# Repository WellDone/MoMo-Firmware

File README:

This file should eventually contain things.

TODO
1.  Fix the alarm handler in the rtcc code to have a common interrupt handler
    and store a pointer to the command to execute.
2.  Add rtcc commands to serial terminal
3.  Add SPI talking to flash memory

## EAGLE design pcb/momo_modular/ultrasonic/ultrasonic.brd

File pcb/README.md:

# MoMo Printed Circuit Boards
This directory contains all of the MoMo PCB files as well as scripts used to convert them into production data.
All boards must use EAGLE CAD for layout in order to be compatible with our production scripts.

## PCB Layout
The MoMo build system includes a set of python based tools used to automatically generate production files, BOMS 
and cost estimates from EAGLE board files.  In order for a board to be compatible with these scripts, it
must be made to conform with the following requirements.

EAGLE Attributes are used to tag each part and board with metadata that enables the scripts to look up
information on the part using the Octopart API and to generate a BOM.  Each part should have one of following attributes:

 * _DIGIKEY-PN_ - This should contain the Digikey part number for this part.  If there is not a digikey part number, is should
be left blank or non existent
 * _MPN_ - This is the Manufacturer's part number for the part.  Either MPN or DIGIKEY-PN must be set for every part on the board that
should be populated.
 * _MANU_ - The manufacturer's name.  If MPN is used to specify the part, MANU should be specified as well.
 * _FOOTPRINT_ - If the part does not have a standard SMD footprint link 0402, 0603, etc, they FOOTPRINT should be explicitly defined so
 that it can be used to create a BOM automatically.  If this is a through hole part, the footprint should be given as "Through Hole"
 * _DESC_ - If the part cannot have a generic description made for it (currently only works for Resistors, Capacitors and Inductors)
 then the explicit description should be given in this attribute.

###Assembly Variants
In order to save on PCB fabrication costs, sometimes a single circuit board will be made flexible so that it can be customized at assembly
time by simply change or not populating certain parts.  Each different way the same board can be assembled is called an Assembly Variant.

If a board has several assembly variants, this should be indicated by specifying certain attributes on the board.  An assembly variant can 
either populate a certain part, not populate a certain part or replace a part with a different one.  To do this, change the DIGIKEY-PN or MPN attribute for the part to contain -VARIANT where variant is the name of the assembly variant.  A part with only DIGIKEY-PN (or MPN) set will be assumed to be populated
in every assembly variant. A part with DIGIKEY-PN-VAR1 and DIGIKEY-PN-VAR2 will be populated only in Assembly Variants VAR1 and VAR2.  

A part with DIGIKEY-PN will be populated in every assembly variant except those that have a DIGIKEY-PN-VAR1 with an empty value.  This
means that the way to not populate a certain part in an assembly variant is to define its part number to be blank.  For library parts
that contain a default DIGIKEY-PN value that is not deletable, this is the only way to not populate a part in an assembly variant.

####Changing Part Values in Different Assembly Variants
Often a different assembly variant will not just populate or depopulate a part, but will change a part's value in order to achieve the desired effect.  
For example, a buck regulator design that can be configured to output either 3.6 or 5V depending on the assembly variant may require just changing the feedback resistor value.
In order to do this, the value should be specified as a VALUE attribute with the appropriate -VARIANT name.  So, if there are 2 assembly variants, 5V and 3V and a resistor is 10K in the 
5V version and 15K in the 3V version, the resistor should have the following two attributes:
VALUE-5V = 10K
VALUE-3V = 15K
The actual value of the part may be set to anything since it will be overriden by these attributes.  It is recommended that the actual part value be set to 'varies' so that the 
schematic's intent is not confusing.
###Global Attributes
Every board must define the following global attributes.  These should be defined on the Board, not the Schematic, under Edit->Global Attributes:

 * _[VARIANT]_ - for each assembly variant (if there is only one, nothing must be done) with value ASSY-VARIANT.  The attribute name is the variant name
 * _WIDTH_ - the width of the board (in inches)
 * _HEIGHT_ - the height of the board (in inches)
 * _REVISION_ - a tag specifying the revision level of the board
 * _PARTNAME_ - a name for the board that will be used to generate file names

###Required Configuration
In order to use these scripts you need to configure the location of the Eagle binary on your computer in /config/settings.local.json.  Use the template provided in:
settings.global.json

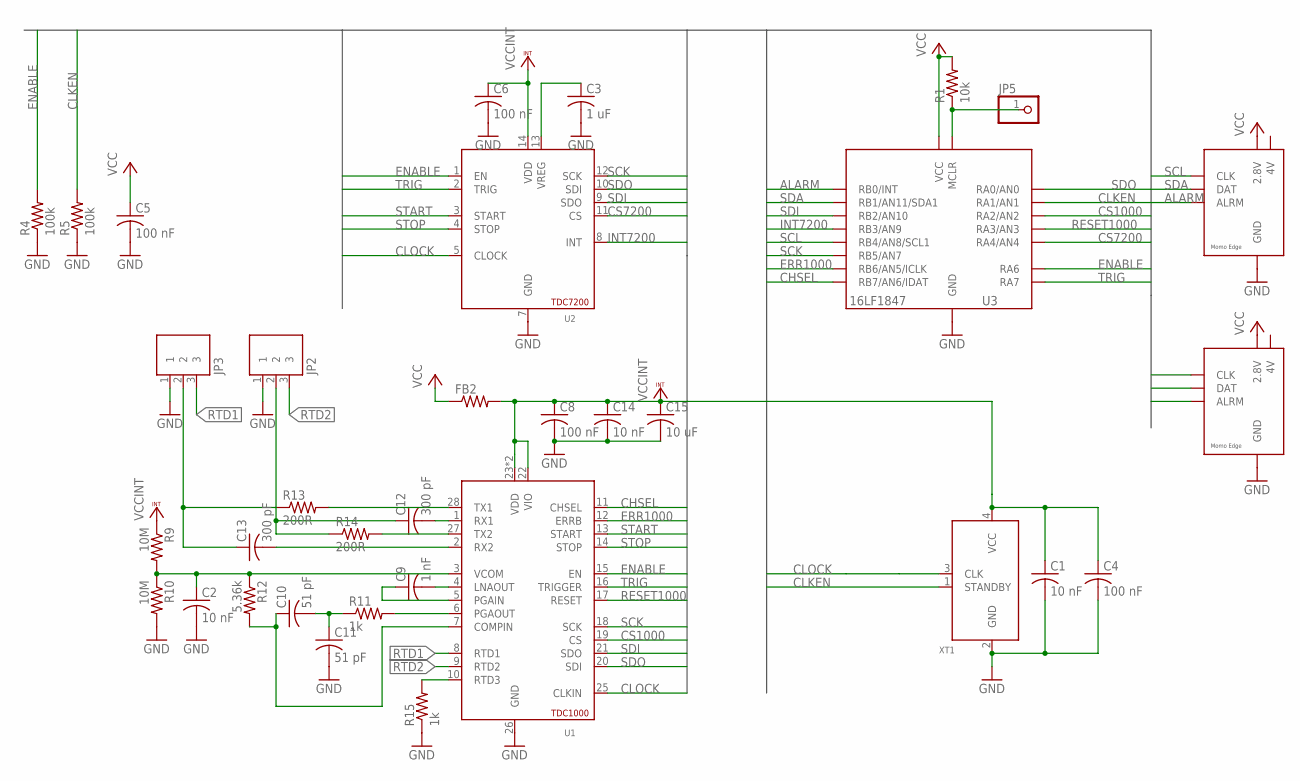
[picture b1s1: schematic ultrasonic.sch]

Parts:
C1, C2, C14: 10 nF; C0402; DIGIKEY-PN 490-4516-1-ND
C3: 1 uF; C0402; DIGIKEY-PN 490-3890-1-ND
C4, C5, C6, C8: 100 nF; C0402; DIGIKEY-PN 490-1318-1-ND
C9: 1 nF; C0402; DIGIKEY-PN 490-6349-1-ND
C10, C11: 51 pF; C0402; DIGIKEY-PN 490-5944-1-ND
C12, C13: 300 pF; C0402; DIGIKEY-PN 490-3234-1-ND
C15: 10 uF; C0805K; DIGIKEY-PN 490-10516-1-ND
FB2: R-US_R0603; R0603
JP1: MOMO-VERT-6M; 1X06
JP2, JP3: JST-PH-3PIN
JP4: MOMO-EDGE-6M-RIGHT; MOMO-EDGE-6M
JP5: PINHD-1X1; 1X01
R1: 10k; R0402; DIGIKEY-PN RHM10.0KCDCT-ND
R4, R5: 100k; R0402; DIGIKEY-PN RHM100KCDCT-ND
R9, R10: 10M; R0402; DIGIKEY-PN 1276-3434-1-ND
R11: 1k; R0402; DIGIKEY-PN RHM1.00KCDCT-ND
R12: 5.36k; R0402; DIGIKEY-PN RHM5.36KCDCT-ND
R13, R14: 200R; R0402; DIGIKEY-PN 311-200LRCT-ND
R15: 1k; R0402; DIGIKEY-PN P1.0KDCCT-ND
U1: TDC1000; TSSOP28; MPN TDC1000PW
U2: TDC7200; TSSOP14; MPN TDC7200PW
U3: PIC16LF1847; SSOP20
XT1: MEMS-OSCILLATOR; 4-DFN

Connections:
4V: JP1.6 (4V), JP4.CLK (4V)
ALARM: JP1.5 (ALRM), JP4.DAT (ALRM), U3.7 (RB0/INT)
CHSEL: U1.11 (CHSEL), U3.14 (RB7/AN6/IDAT)
CLKEN: R5.2, U3.20 (RA1/AN1), XT1.1 (STANDBY)
CLOCK: U1.25 (CLKIN), U2.5 (CLOCK), XT1.3 (CLK)
CS1000: U1.19 (CS), U3.1 (RA2/AN2)
CS7200: U2.11 (CS), U3.3 (RA4/AN4)
ENABLE: R4.2, U1.15 (EN), U2.1 (EN), U3.17 (RA6)
ERR1000: U1.12 (ERRB), U3.13 (RB6/AN5/ICLK)
GND: C1.2, C2.2, C3.2, C4.2, C5.2, C6.2, C8.2, C11.2, C14.2, C15.2, JP1.7 (GND), JP2.1, JP3.1, JP4.V28 (GND), R4.1, R5.1, R10.2, R15.1, U1.26 (GND), U2.7 (GND), U3.5 (GND), U3.6 (GND), XT1.2 (GND)
INT7200: U2.8 (INT), U3.10 (RB3/AN9)
unnamed: C3.1, U2.13 (VREG)
unnamed: C9.2, U1.4 (LNAOUT)
unnamed: JP5.1, R1.1, U3.4 (MCLR)
unnamed: C2.1, R9.2, R10.1, R12.1, U1.3 (VCOM)
unnamed: C9.1, U1.5 (PGAIN)
unnamed: C10.2, C11.1, R11.1
unnamed: R11.2, U1.6 (PGAOUT)
unnamed: C10.1, R12.2, U1.7 (COMPIN)
unnamed: C13.1, JP3.2, R13.1
unnamed: R14.2, U1.27 (TX2)
unnamed: R13.2, U1.28 (TX1)
unnamed: C12.2, U1.1 (RX1)
unnamed: C13.2, U1.2 (RX2)
unnamed: C12.1, JP2.2, R14.1
unnamed: R15.2, U1.10 (RTD3)
RESET1000: U1.17 (RESET), U3.2 (RA3/AN3)
RTD1: JP3.3, U1.8 (RTD1)
RTD2: JP2.3, U1.9 (RTD2)
SCK: U1.18 (SCK), U2.12 (SCK), U3.12 (RB5/AN7)
SCL: JP1.3 (CLK), JP4.4V (CLK), U3.11 (RB4/AN8/SCL1)
SDA: JP1.4 (DAT), JP4.ALARM (DAT), U3.8 (RB1/AN11/SDA1)
SDI: U1.21 (SDO), U2.9 (SDO), U3.9 (RB2/AN10)
SDO: U1.20 (SDI), U2.10 (SDI), U3.19 (RA0/AN0)
START: U1.13 (START), U2.3 (START)
STOP: U1.14 (STOP), U2.4 (STOP)
TRIG: U1.16 (TRIGGER), U2.2 (TRIG), U3.18 (RA7)
VCC: C5.1, FB2.1, JP1.1 (2.8V), JP4.GND (2.8V), R1.2, U3.15 (VCC), U3.16 (VCC)
VCCINT: C1.1, C4.1, C6.1, C8.1, C14.1, C15.1, FB2.2, R9.1, U1.22 (VIO), U1.23 (VDD), U1.24 (VDD), U2.14 (VDD), XT1.4 (VCC)

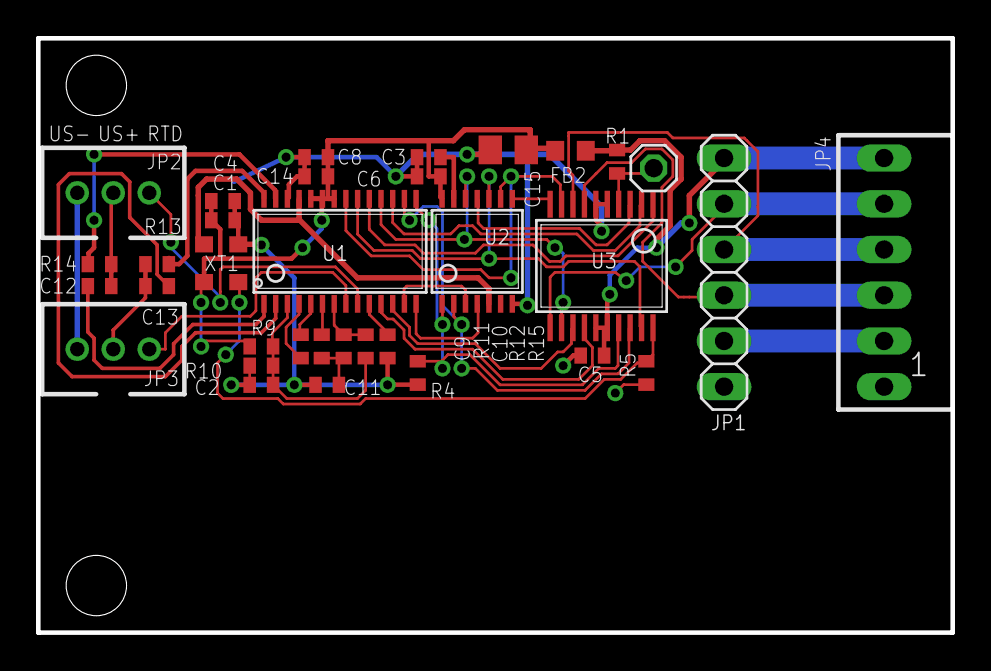
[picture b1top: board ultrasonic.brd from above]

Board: 2 copper layers, 50.8 x 33.0 mm, 34 parts (0 on the bottom side), 39 nets.

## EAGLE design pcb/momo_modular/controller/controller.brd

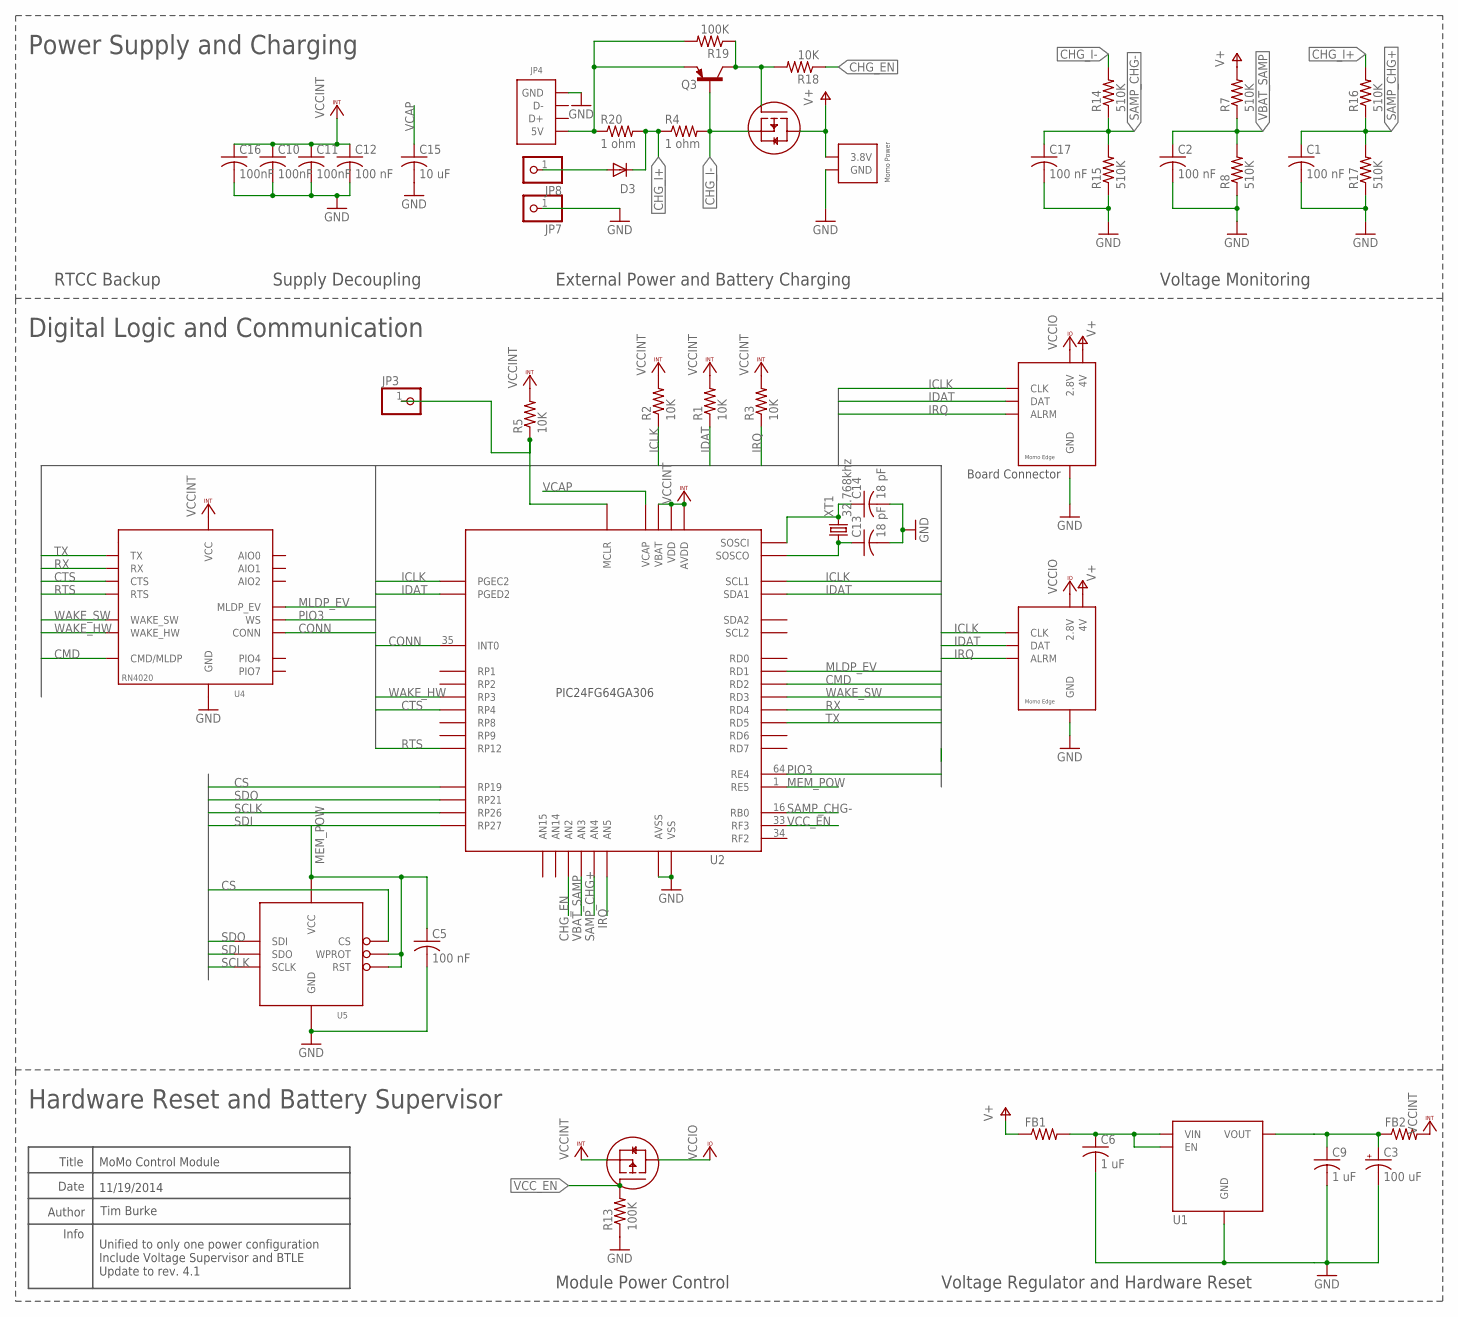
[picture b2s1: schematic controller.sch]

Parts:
C1, C2, C5, C12, C17: 100 nF; C0402K; DIGIKEY-PN 445-1265-1-ND
C3: 100 uF; B/3528-21R; DIGIKEY-PN 478-8156-1-ND
C6, C9: 1 uF; C0402K; DIGIKEY-PN 445-4114-1-ND
C10, C11, C16: 100nF; C0402K; DIGIKEY-PN 445-1265-1-ND
C13, C14: 18 pF; C0402K; DIGIKEY-PN 445-1238-1-ND
C15: 10 uF; C0805K; DIGIKEY-PN 1276-2893-1-ND
D3: DIODE-SC79_INFINEON; SC79_INFINEON
FB1, FB2: R-US_R0603; R0603; DIGIKEY-PN 490-5981-1-ND
JP1: MOMO-VERT-6M; 1X06; DIGIKEY-PN S1011EC-06-ND
JP2: MOMO-EDGE-6F; MOMO-EDGE-8F
JP3, JP7, JP8: PINHD-1X1; 1X01
JP4: CONN-MICROUSB-B-RCPT; MICROUSB-B-FCI
JP5: MOMO-PWR-HOUSED
Q2, Q4: P-MOSFET; SOT23; DIGIKEY-PN IRLML6402PBFCT-ND
Q3: MMBTA56-SOT23; SOT23; DIGIKEY-PN 568-1742-1-ND
R1, R2, R3, R5, R18: 10K; R0603; DIGIKEY-PN P10.0KHCT-ND
R4, R20: 1 ohm; R1206; DIGIKEY-PN 311-1.00FRCT-ND
R7, R8, R14, R15, R16, R17: 510K; R0603; DIGIKEY-PN P510KHCT-ND
R13, R19: 100K; R0603; DIGIKEY-PN P100KHCT-ND
U1: XC6504-LINEAR-REGULATOR; SOT23-5L
U2: PIC24FJ64GA306; TQFP64-10X10
U4: RN4020_BT_4.0_MODULE; RN20-BTLE-MODULE; DIGIKEY-PN RN4020-V/RM120-ND
U5: FLASH8MSOP8; SOP08; DIGIKEY-PN M25PX80-VMN6TPCT-ND
XT1: 32.768khz; TC26H; DIGIKEY-PN 535-9034-ND

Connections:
CHG_EN: R18.1, U2.14 (AN2)
CHG_I+: D3.C, R4.1, R16.2, R20.2
CHG_I-: Q3.1 (B), Q4.2 (SOURCE), R4.2, R14.2
CMD: U2.50 (RD2), U4.CMD/MLDP
CONN: U2.35 (INT0), U4.PIO1 (CONN)
CS: U2.6 (RP19), U5.1 (CS)
CTS: U2.43 (RP4), U4.PIO5 (CTS)
GND: C1.2, C2.2, C3.-, C5.2, C6.2, C9.2, C10.2, C11.2, C12.2, C13.2, C14.2, C15.2, C16.2, C17.2, JP1.7 (GND), JP2.GND, JP4.5 (GND), JP4.GND2 (GND), JP4.GND3 (GND), JP4.GND4 (GND), JP4.GND5 (GND), JP4.GND6 (GND), JP5.2 (GND), JP7.1, R8.1, R13.1, R15.1, R17.1, U1.2 (GND), U2.9 (VSS), U2.20 (AVSS), U2.25 (VSS), U2.41 (VSS), U4.GND, U4.GND1 (GND), U4.SHIELD1 (GND), U4.SHIELD2 (GND), U4.SHIELD3 (GND), U4.SHIELD4 (GND), U5.4 (GND)
ICLK: JP1.3 (CLK), JP2.CLK, R2.1, U2.17 (PGEC2), U2.37 (SCL1)
IDAT: JP1.4 (DAT), JP2.DAT, R1.1, U2.18 (PGED2), U2.36 (SDA1)
IRQ: JP1.5 (ALRM), JP2.ARLM (ALRM), R3.1, U2.11 (AN5)
MEM_POW: C5.1, U2.1 (RE5), U5.3 (WPROT), U5.7 (RST), U5.8 (VCC)
MLDP_EV: U2.49 (RD1), U4.PIO2 (MLDP_EV)
unnamed: C3.+, C9.1, FB2.1, U1.5 (VOUT)
unnamed: C6.1, FB1.2, U1.1 (VIN), U1.3 (EN)
unnamed: D3.A, JP8.1
unnamed: JP3.1, R5.1, U2.7 (MCLR)
unnamed: JP4.1 (5V), Q3.2 (E), R19.2, R20.1
unnamed: C14.1, U2.47 (SOSCI), XT1.2
unnamed: C13.1, U2.48 (SOSCO), XT1.1
unnamed: Q3.3 (C), Q4.1 (GATE), R18.2, R19.1
PIO3: U2.64 (RE4), U4.PIO3 (WS)
RTS: U2.45 (RP12), U4.RTS/PIO6 (RTS)
RX: U2.52 (RD4), U4.UART_RX (RX)
SAMP_CHG+: C1.1, R16.1, R17.2, U2.12 (AN4)
SAMP_CHG-: C17.1, R14.1, R15.2, U2.16 (RB0)
SCLK: U2.5 (RP26), U5.6 (SCLK)
SDI: U2.8 (RP27), U5.2 (SDO)
SDO: U2.4 (RP21), U5.5 (SDI)
TX: U2.53 (RD5), U4.UART_TX (TX)
V+: FB1.1, JP1.6 (4V), JP2.V4 (4V), JP5.1 (3.8V), Q4.3 (DRAIN), R7.2
VBAT_SAMP: C2.1, R7.1, R8.2, U2.13 (AN3)
VCAP: C15.1, U2.56 (VCAP)
VCCINT: C10.1, C11.1, C12.1, C16.1, FB2.2, Q2.2 (SOURCE), R1.2, R2.2, R3.2, R5.2, U2.10 (VDD), U2.19 (AVDD), U2.26 (VDD), U2.38 (VDD), U2.57 (VBAT), U4.VDD (VCC)
VCCIO: JP1.1 (2.8V), JP2.V28 (2.8V), Q2.3 (DRAIN)
VCC_EN: Q2.1 (GATE), R13.2, U2.33 (RF3)
WAKE_HW: U2.44 (RP3), U4.WAKE_HW
WAKE_SW: U2.51 (RD3), U4.WAKE_SW

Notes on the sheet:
Title
Author
Date
Tim Burke
Info
Board Connector
MoMo Control Module
11/19/2014
Unified to only one power configuration Include Voltage Supervisor and BTLE Update to rev. 4.1
Power Supply and Charging
Digital Logic and Communication
Voltage Monitoring
External Power and Battery Charging
Supply Decoupling
RTCC Backup
Hardware Reset and Battery Supervisor
Module Power Control
Voltage Regulator and Hardware Reset

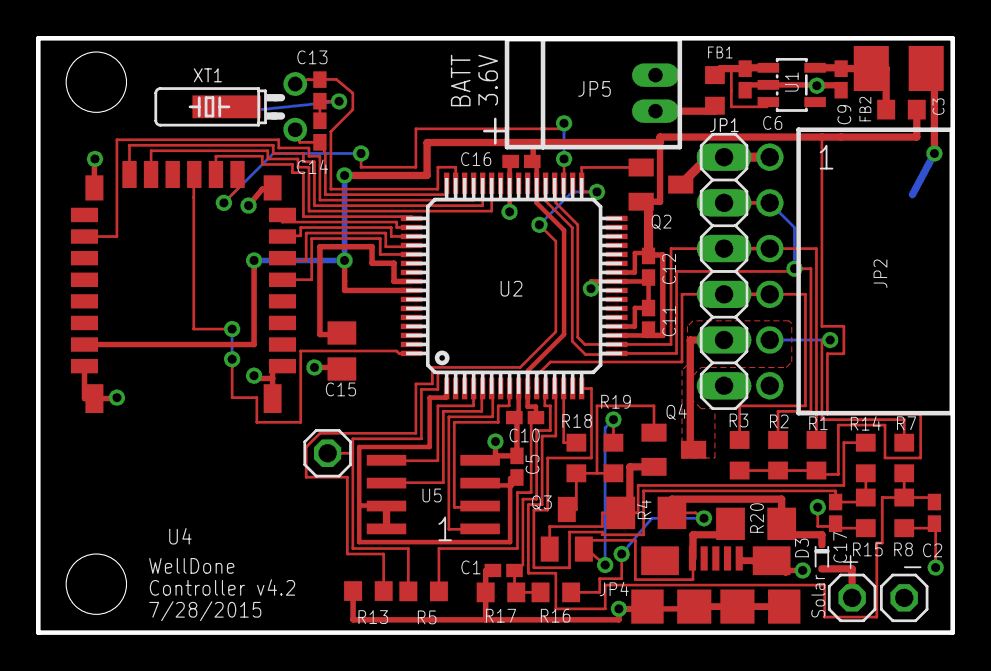
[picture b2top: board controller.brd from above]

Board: 2 copper layers, 50.8 x 33.0 mm, 47 parts (0 on the bottom side), 38 nets.

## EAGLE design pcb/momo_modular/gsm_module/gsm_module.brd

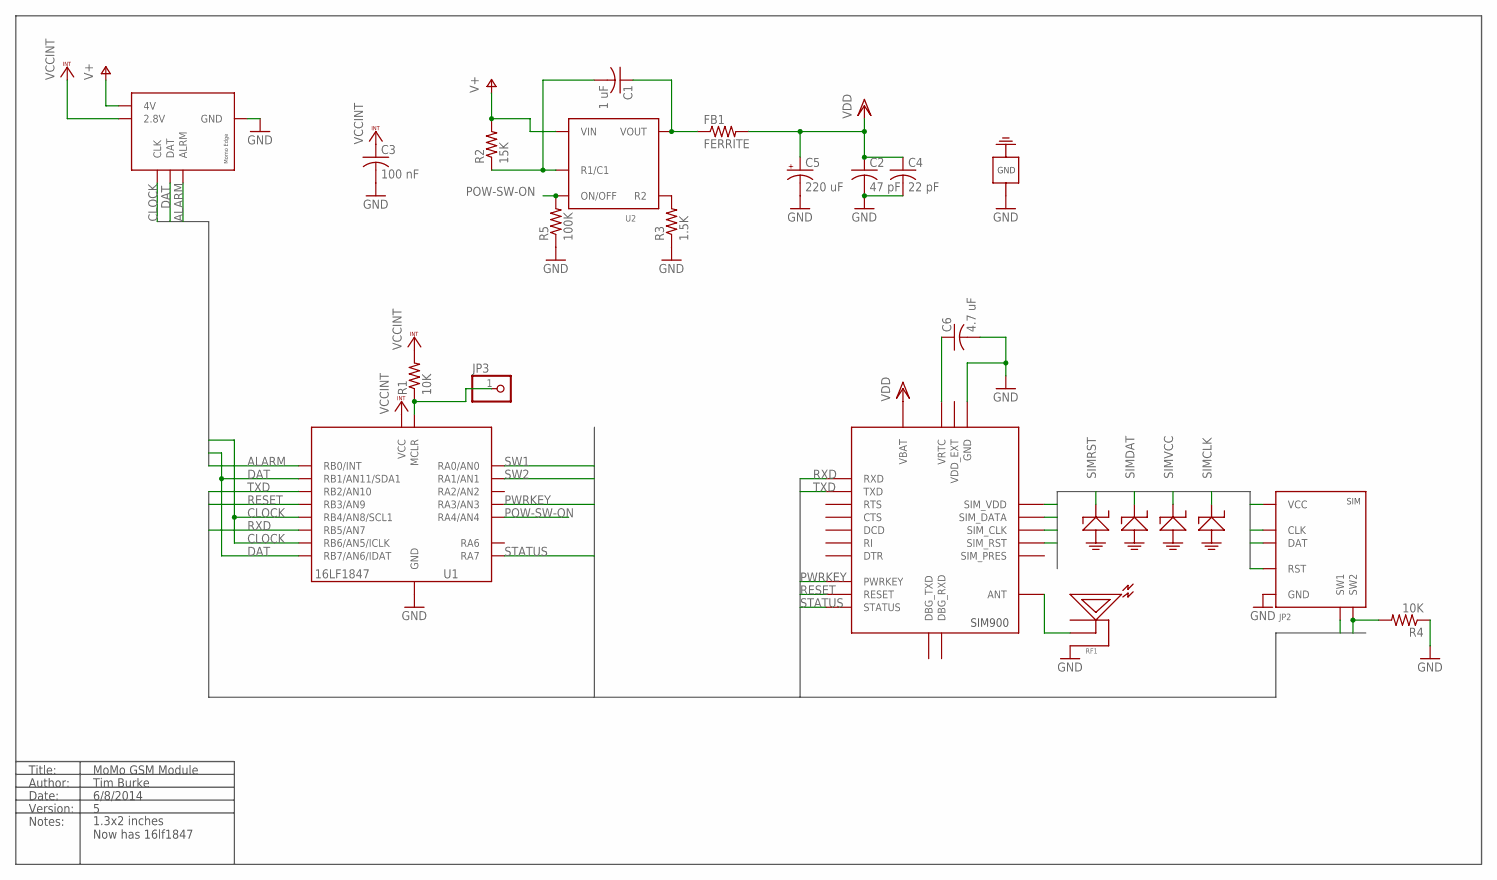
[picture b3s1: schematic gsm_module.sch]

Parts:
C1: 1 uF; C0402K; DIGIKEY-PN 445-4114-1-ND
C2: 47 pF; C0402K; DIGIKEY-PN 445-1243-1-ND
C3: 100 nF; C0402; DIGIKEY-PN 445-1265-1-ND
C4: 22 pF; C0402K; DIGIKEY-PN 445-1239-1-ND
C5: 220 uF; CT3528
C6: 4.7 uF; C0805; DIGIKEY-PN 1276-1259-1-ND
FB1: FERRITE; R0805; DIGIKEY-PN 445-1567-1-ND
JP1: MOMO-EDGE-6M
JP2: SIMHOLDER-8PINMICROSIM; MOLEX-MICROSIM-0787270001
JP3: PINHD-1X1; 1X01
R1, R4: 10K; R0603; DIGIKEY-PN P10.0KHCT-ND
R2: 15K; R0603; DIGIKEY-PN P15KGCT-ND
R3: 1.5K; R0603; DIGIKEY-PN P1.5KGCT-ND
R5: 100K; R0603; DIGIKEY-PN P100KHCT-ND
RF1: RFANTENNA; RFJACK; DIGIKEY-PN J983CT-ND
U1: PIC16LF1847; SSOP20
U2: TI-HIGHSIDE-PFET; SOT23-6L
U3: SIM900
U4: ESD-SMF05C; SC70-6L

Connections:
ALARM: JP1.ALARM (ALRM), U1.7 (RB0/INT)
CLOCK: JP1.CLK, U1.11 (RB4/AN8/SCL1), U1.13 (RB6/AN5/ICLK)
DAT: JP1.DAT, U1.8 (RB1/AN11/SDA1), U1.14 (RB7/AN6/IDAT)
GND: C2.2, C3.2, C4.2, C5.-, C6.2, JP1.GND, JP2.C5 (GND), JP2.GND1 (GND), JP2.GND2 (GND), JP2.GND3 (GND), JP2.GND4 (GND), JP2.GND5 (GND), JP2.GND6 (GND), R3.1, R4.1, R5.1, RF1.UNUSED1 (SHIELD), RF1.UNUSED2 (SHIELD), U1.5 (GND), U1.6 (GND), U3.17 (GND), U3.18 (GND), U3.29 (GND), U3.39 (GND), U3.45 (GND), U3.46 (GND), U3.53 (GND), U3.54 (GND), U3.58 (GND), U3.59 (GND), U3.61 (GND), U3.62 (GND), U3.63 (GND), U3.64 (GND), U3.65 (GND), U4.2 (GND)
unnamed: R3.2, U2.1 (R2)
unnamed: JP3.1, R1.1, U1.4 (MCLR)
unnamed: C1.2, R2.1, U2.6 (R1/C1)
unnamed: C1.1, FB1.1, U2.2 (VOUT), U2.3 (VOUT)
unnamed: C6.1, U3.26 (VRTC)
unnamed: RF1.ANTENNA (PIN), U3.60 (ANT)
POW-SW-ON: R5.2, U1.3 (RA4/AN4), U2.5 (ON/OFF)
PWRKEY: U1.2 (RA3/AN3), U3.1 (PWRKEY)
RESET: U1.10 (RB3/AN9), U3.16 (RESET)
RXD: U1.12 (RB5/AN7), U3.10 (RXD)
SIMCLK: JP2.C3 (CLK), U3.32 (SIM_CLK), U4.3
SIMDAT: JP2.C7 (DAT), U3.31 (SIM_DATA), U4.5
SIMRST: JP2.C2 (RST), U3.33 (SIM_RST), U4.1
SIMVCC: JP2.C1 (VCC), U3.30 (SIM_VDD), U4.4
STATUS: U1.18 (RA7), U3.66 (STATUS)
SW1: JP2.DCONT (SW1), U1.19 (RA0/AN0)
SW2: JP2.DSPRING (SW2), R4.2, U1.20 (RA1/AN1)
TXD: U1.9 (RB2/AN10), U3.9 (TXD)
V+: JP1.4V, R2.2, U2.4 (VIN)
VCCINT: C3.1, JP1.V28 (2.8V), R1.2, U1.15 (VCC), U1.16 (VCC)
VDD: C2.1, C4.1, C5.+, FB1.2, U3.55 (VBAT), U3.56 (VBAT), U3.57 (VBAT)
VDD_EXT: U3.15 (VDD_EXT)

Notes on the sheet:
Title:
Author:
Date:
Version:
Notes:
MoMo GSM Module
Tim Burke
6/8/2014
1.3x2 inches Now has 16lf1847

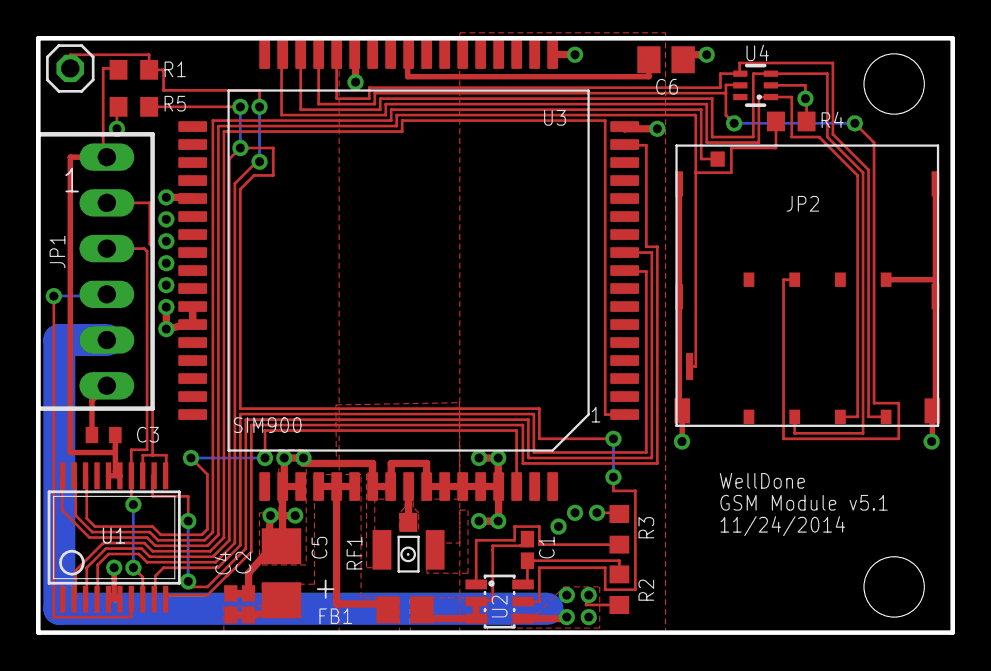
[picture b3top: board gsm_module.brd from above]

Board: 2 copper layers, 50.8 x 33.0 mm, 20 parts (0 on the bottom side), 25 nets.

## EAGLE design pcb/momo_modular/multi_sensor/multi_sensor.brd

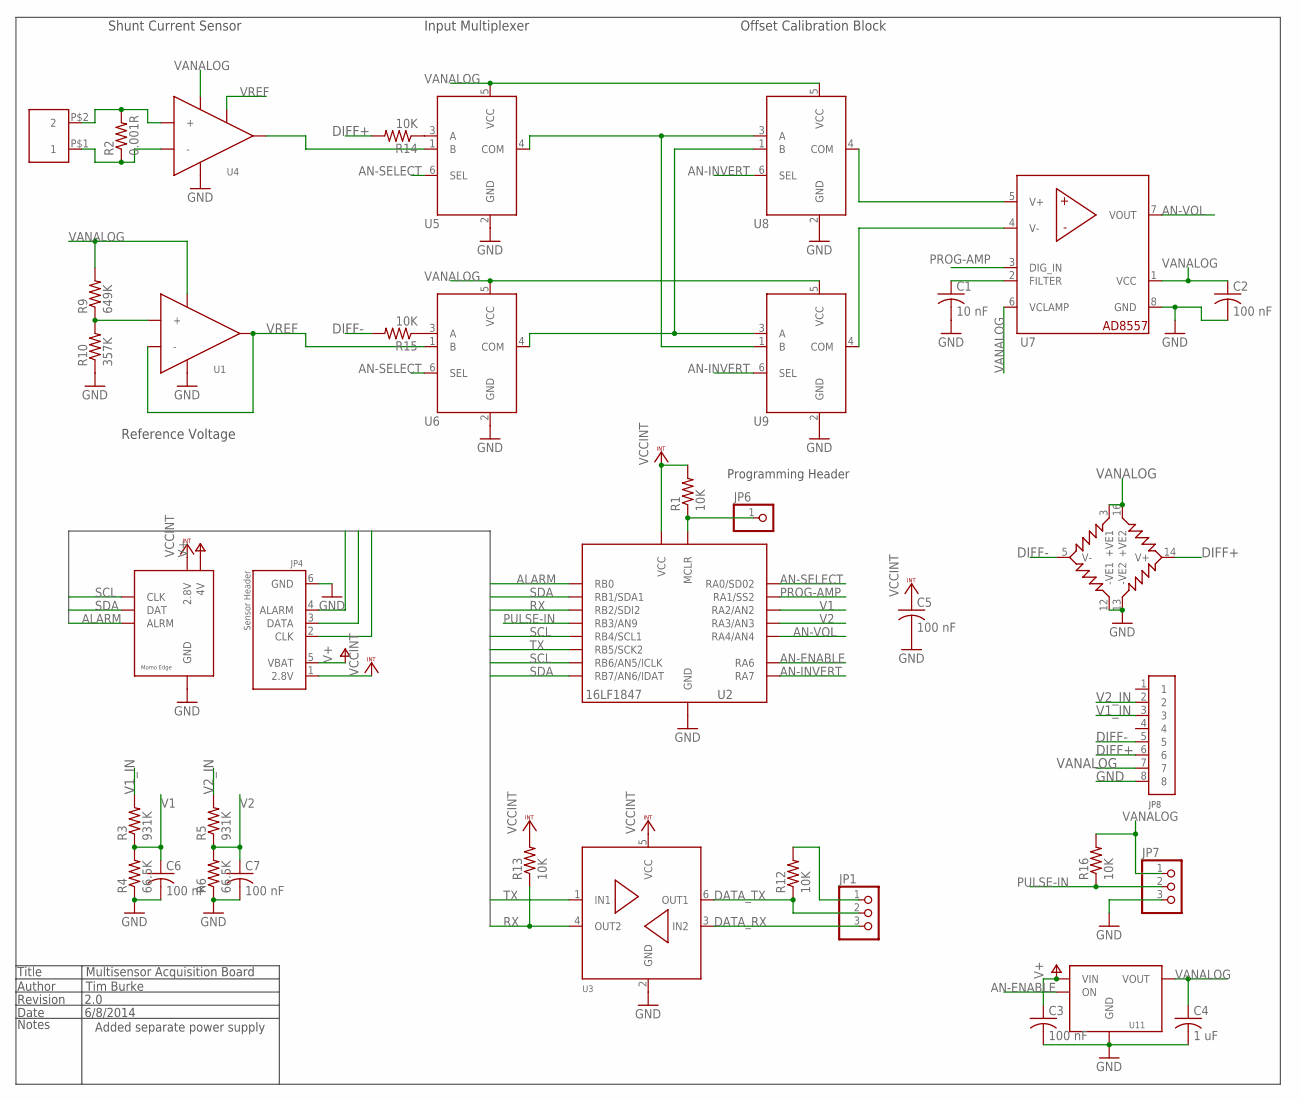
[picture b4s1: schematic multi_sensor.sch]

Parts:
C1: 10 nF; C0402; DIGIKEY-PN 490-6286-1-ND
C2, C3, C5, C6, C7: 100 nF; C0402K; DIGIKEY-PN 445-1265-1-ND
C4: 1 uF; C0402K; DIGIKEY-PN 445-4114-1-ND
JP1, JP7: PINHD-1X3; 1X03
JP2: MOMO-VERT-6M; 1X06; DIGIKEY-PN S7004-ND
JP3: 5MM-SCREWTERM-2POS; 5MM-SCREWTERM
JP4: MOMO-SENSOR-RJ11; RJ-12; DIGIKEY-PN AE10371-ND
JP6: PINHD-1X1; 1X01
JP8: 8PIN-TERMBLOCK-PUSH; 8-PIN-TERMBLOCK-PUSH
R1, R12, R13, R14, R15, R16: 10K; R0603; DIGIKEY-PN P10.0KHCT-ND
R2: 0.001R; R2512; DIGIKEY-PN CRF2512-FV-R001ELFCT-ND
R3, R5: 931K; R0603; DIGIKEY-PN RHM931KCLCT-ND
R4, R6: 66.5K; R0603; DIGIKEY-PN RC0603FR-0766K5L
R9: 649K; R0603; DIGIKEY-PN 311-649KHRCT-ND
R10: 357K; R0603; DIGIKEY-PN RC0603FR-07357KL
U1: MCP6001U; SOT23-5L
U2: 16LF1847; SSOP20; DIGIKEY-PN PIC16LF1847-I/SS-ND
U3: DUAL-BUFFER-OD-NC7WZ07; SC70-6L
U4: LT1990; SOP08
U5, U6, U8, U9: 2:1-MUX; SOT363_INFINEON
U7: AD8557-DIGITRIM-OPAMP; SOIC8
U10: SM5470-DIFF-PRESS-SENSOR; SO16W
U11: TCR2EF28-LINREG; SC74A-5PIN

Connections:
ALARM: JP2.5 (ALRM), JP4.4 (ALARM), U2.7 (RB0)
AN-ENABLE: U2.17 (RA6), U11.3 (ON)
AN-INVERT: U2.18 (RA7), U8.6 (SEL), U9.6 (SEL)
AN-SELECT: U2.19 (RA0/SD02), U5.6 (SEL), U6.6 (SEL)
AN-VOL: U2.3 (RA4/AN4), U7.7 (VOUT)
DATA_RX: JP1.3, U3.3 (IN2)
DATA_TX: JP1.2, R12.1, U3.6 (OUT1)
DIFF+: JP8.6, R14.2, U10.14 (V+)
DIFF-: JP8.5, R15.2, U10.5 (V-)
GND: C1.2, C2.2, C3.2, C4.2, C5.2, C6.2, C7.2, JP2.7 (GND), JP4.6 (GND), JP7.3, JP8.8, R4.1, R6.1, R10.1, U1.2 (GND), U2.5 (GND), U2.6 (GND), U3.2 (GND), U4.4 (GND), U5.2 (GND), U6.2 (GND), U7.8 (GND), U8.2 (GND), U9.2 (GND), U10.12 (-VE1), U10.13 (-VE2), U11.2 (GND)
unnamed: JP1.1, R12.2
unnamed: R9.1, R10.2, U1.1 (+)
unnamed: JP6.1, R1.1, U2.4 (MCLR)
unnamed: U5.4 (COM), U8.3 (A), U9.1 (B)
unnamed: R14.1, U5.3 (A)
unnamed: C1.1, U7.2 (FILTER)
unnamed: U6.4 (COM), U8.1 (B), U9.3 (A)
unnamed: R15.1, U6.3 (A)
unnamed: U7.5 (V+), U8.4 (COM)
unnamed: U7.4 (V-), U9.4 (COM)
unnamed: U4.6 (OUT), U5.1 (B)
PROG-AMP: U2.20 (RA1/SS2), U7.3 (DIG_IN)
PULSE-IN: JP7.2, R16.1, U2.10 (RB3/AN9)
RS+: JP3.P$1 (1), R2.1, U4.2 (-)
RS-: JP3.P$2 (2), R2.2, U4.3 (+)
RX: R13.1, U2.9 (RB2/SDI2), U3.4 (OUT2)
SCL: JP2.3 (CLK), JP4.2 (CLK), U2.11 (RB4/SCL1), U2.13 (RB6/AN5/ICLK)
SDA: JP2.4 (DAT), JP4.3 (DATA), U2.8 (RB1/SDA1), U2.14 (RB7/AN6/IDAT)
TX: U2.12 (RB5/SCK2), U3.1 (IN1)
V1: C6.1, R3.1, R4.2, U2.1 (RA2/AN2)
V1_IN: JP8.3, R3.2
V2: C7.1, R5.1, R6.2, U2.2 (RA3/AN3)
V2_IN: JP8.2, R5.2
V+: C3.1, JP2.6 (4V), JP4.5 (VBAT), U11.1 (VIN)
VANALOG: C2.1, C4.1, JP7.1, JP8.7, R9.2, R16.2, U1.5 (VCC), U4.7 (VCC), U5.5 (VCC), U6.5 (VCC), U7.1 (VCC), U7.6 (VCLAMP), U8.5 (VCC), U9.5 (VCC), U10.3 (+VE1), U10.16 (+VE2), U11.5 (VOUT)
VCCINT: C5.1, JP2.1 (2.8V), JP4.1 (2.8V), R1.2, R13.2, U2.15 (VCC), U2.16 (VCC), U3.5 (VCC)
VREF: U1.3 (-), U1.4 (OUT), U4.1 (SHUT), U6.1 (B)

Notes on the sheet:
Title
Author
Revision
Date
Notes
Multisensor Acquisition Board
Tim Burke
2.0
6/8/2014
Programming Header
Offset Calibration Block
Input Multiplexer
Shunt Current Sensor
Reference Voltage
Added separate power supply

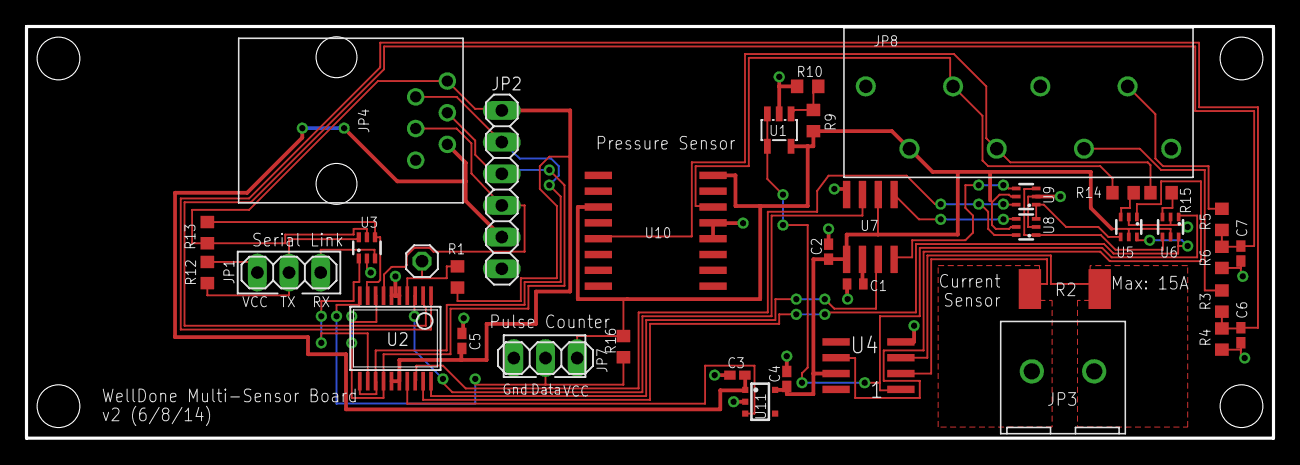
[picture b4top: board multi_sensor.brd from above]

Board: 2 copper layers, 100.0 x 33.0 mm, 38 parts (0 on the bottom side), 37 nets.

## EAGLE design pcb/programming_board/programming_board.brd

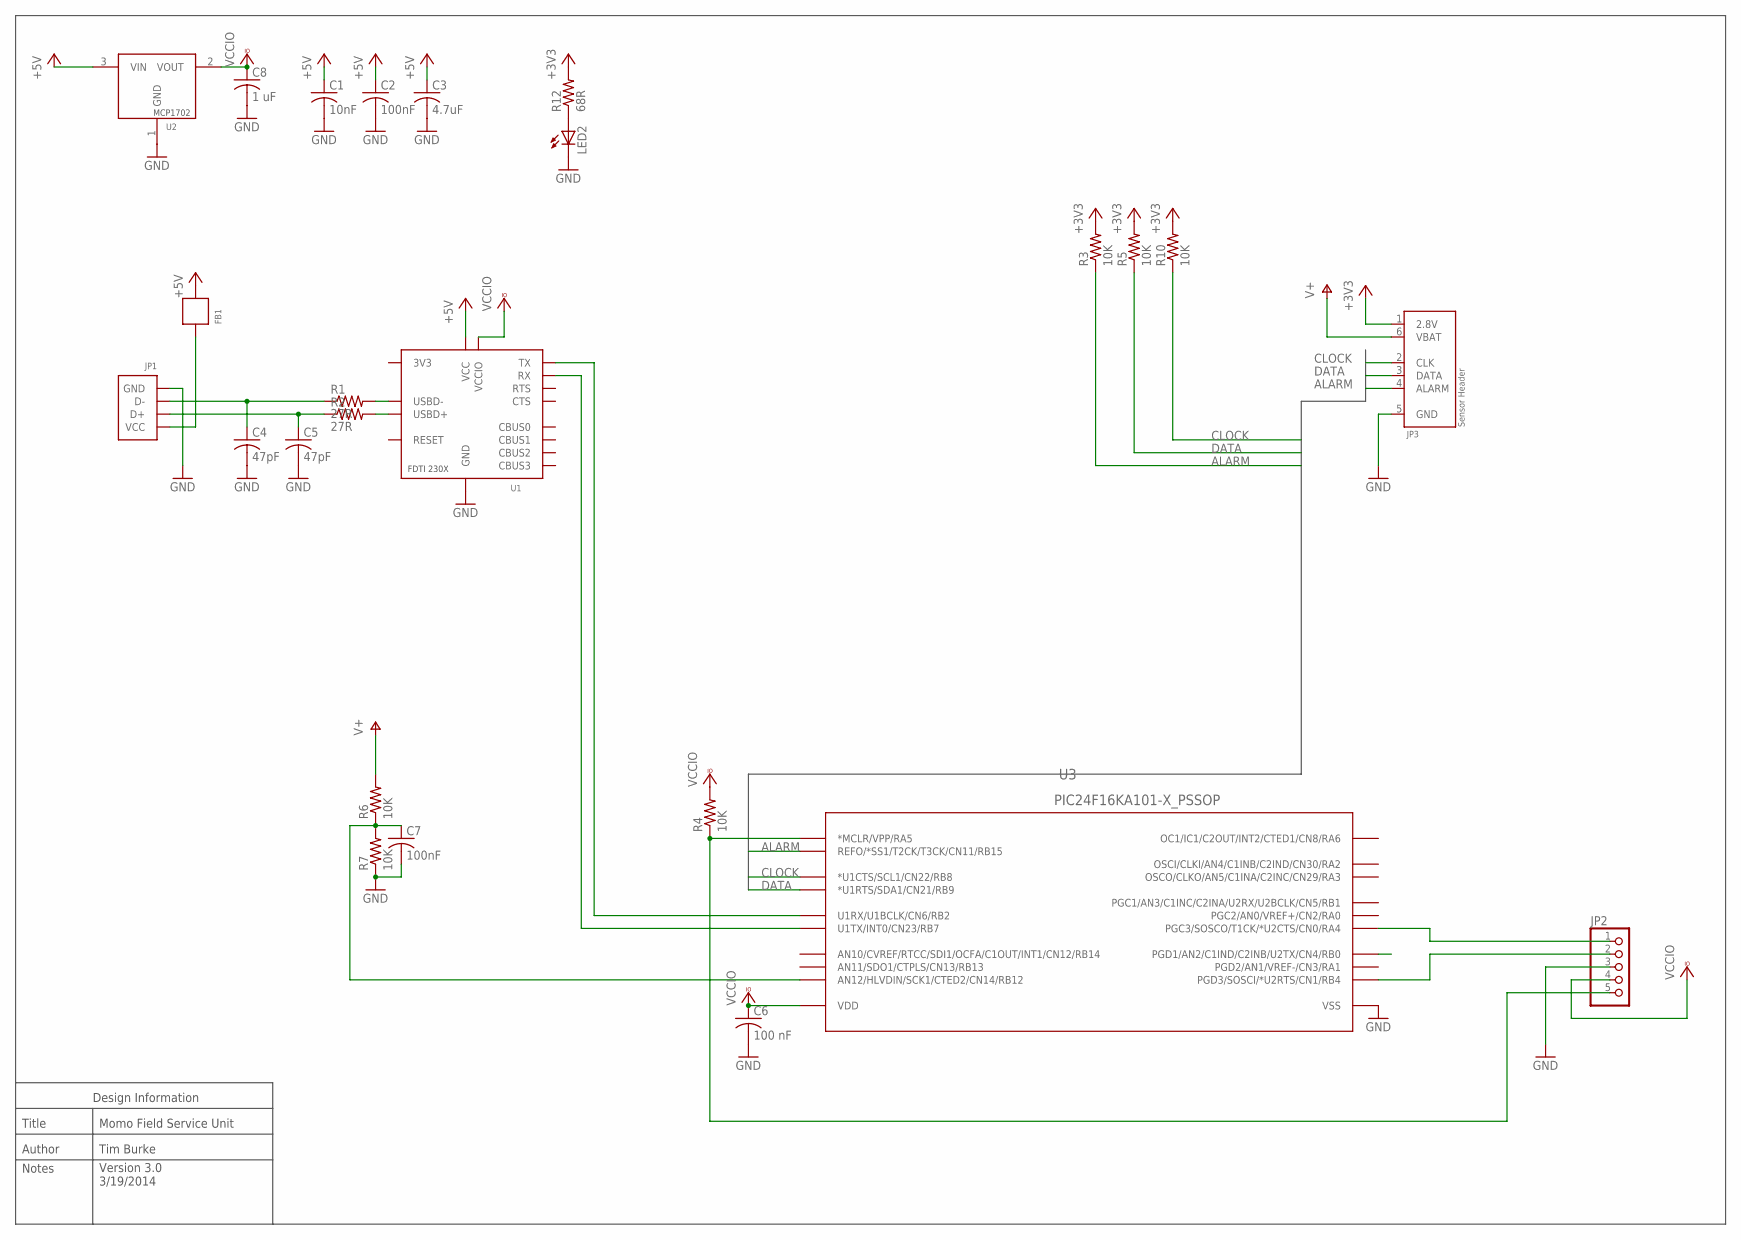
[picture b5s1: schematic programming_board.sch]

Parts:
C1: 10nF; C0402; DIGIKEY-PN 1276-1499-1-ND
C2, C7: 100nF; C0402; DIGIKEY-PN 445-1265-1-ND
C3: 4.7uF; C0805; DIGIKEY-PN 445-1605-1-ND
C4, C5: 47pF; C0402; DIGIKEY-PN 1276-1699-1-ND
C6: 100 nF; C0402; DIGIKEY-PN 445-1265-1-ND
C8: 1 uF; C0402; DIGIKEY-PN 1276-1076-1-ND
FB1: FERRITE; R0805; DIGIKEY-PN 240-2390-1-ND
JP1: MOLEX-USB-CONN; USB-MALE-EDGE
JP2: PINHD-1X5; 1X05
JP3: MOMO-SENSOR-RJ11-VERT; RJ12-VERT
LED2: LEDSML0603; SML0603; DIGIKEY-PN 475-1409-1-ND
R1, R2: 27R; R0603; DIGIKEY-PN P27.0HCT-ND
R3, R4, R5, R6, R7, R10: 10K; R0603; DIGIKEY-PN P10.0KHCT-ND
R12: 68R; R0603; DIGIKEY-PN P68GCT-ND
U1: FTDI-230X; SSOP16; DIGIKEY-PN 768-1135-1-ND
U2: MCP1702; SOT23
U3: PIC24F16KA101-X_PSSOP; SSOP20; DIGIKEY-PN PIC24F16KA101-I/SS-ND

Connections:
+3V3: JP3.1 (2.8V), R3.2, R5.2, R10.2, R12.2
+5V: C1.1, C2.1, C3.1, FB1.2 (OUT), U1.12 (VCC), U2.3 (VIN)
ALARM: JP3.4 (ALARM), R3.1, U3.18 (REFO/*SS1/T2CK/T3CK/CN11/RB15)
CLOCK: JP3.2 (CLK), R10.1, U3.12 (*U1CTS/SCL1/CN22/RB8)
CLOCKRX: U3.4 (PGD1/AN2/C1IND/C2INB/U2TX/CN4/RB0)
DATA: JP3.3 (DATA), R5.1, U3.13 (*U1RTS/SDA1/CN21/RB9)
GND: C1.2, C2.2, C3.2, C4.2, C5.2, C6.2, C7.2, C8.2, JP1.4 (GND), JP2.3, JP3.5 (GND), LED2.C, R7.1, U1.5 (GND), U1.13 (GND), U2.1 (GND), U3.19 (VSS)
unnamed: C4.1, JP1.2 (D-), R1.1
unnamed: FB1.1 (IN), JP1.1 (VCC)
unnamed: C5.1, JP1.3 (D+), R2.1
unnamed: R1.2, U1.9 (USBD-)
unnamed: R2.2, U1.8 (USBD+)
unnamed: LED2.A, R12.1
unnamed: JP2.1, U3.10 (PGC3/SOSCO/T1CK/*U2CTS/CN0/RA4)
unnamed: JP2.2, U3.9 (PGD3/SOSCI/*U2RTS/CN1/RB4)
unnamed: C7.1, R6.1, R7.2, U3.15 (AN12/HLVDIN/SCK1/CTED2/CN14/RB12)
unnamed: JP2.5, R4.1, U3.1 (*MCLR/VPP/RA5)
PICRX1: U1.1 (TX), U3.6 (U1RX/U1BCLK/CN6/RB2)
PICTX1: U1.4 (RX), U3.11 (U1TX/INT0/CN23/RB7)
V+: JP3.6 (VBAT), R6.2
VCCIO: C6.1, C8.1, JP2.4, R4.2, U1.3 (VCCIO), U2.2 (VOUT), U3.20 (VDD)

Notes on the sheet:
Tim Burke
Author
Title
Momo Field Service Unit
Notes
Version 3.0 3/19/2014
Design Information

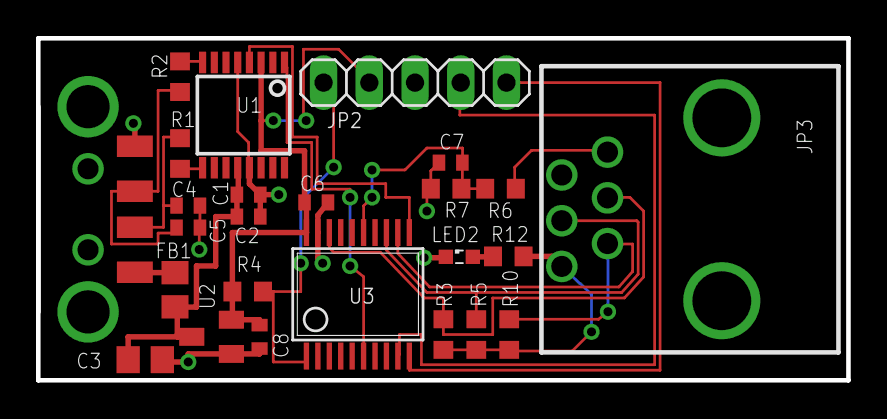
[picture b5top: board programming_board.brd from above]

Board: 2 copper layers, 45.0 x 19.0 mm, 25 parts (0 on the bottom side), 20 nets.

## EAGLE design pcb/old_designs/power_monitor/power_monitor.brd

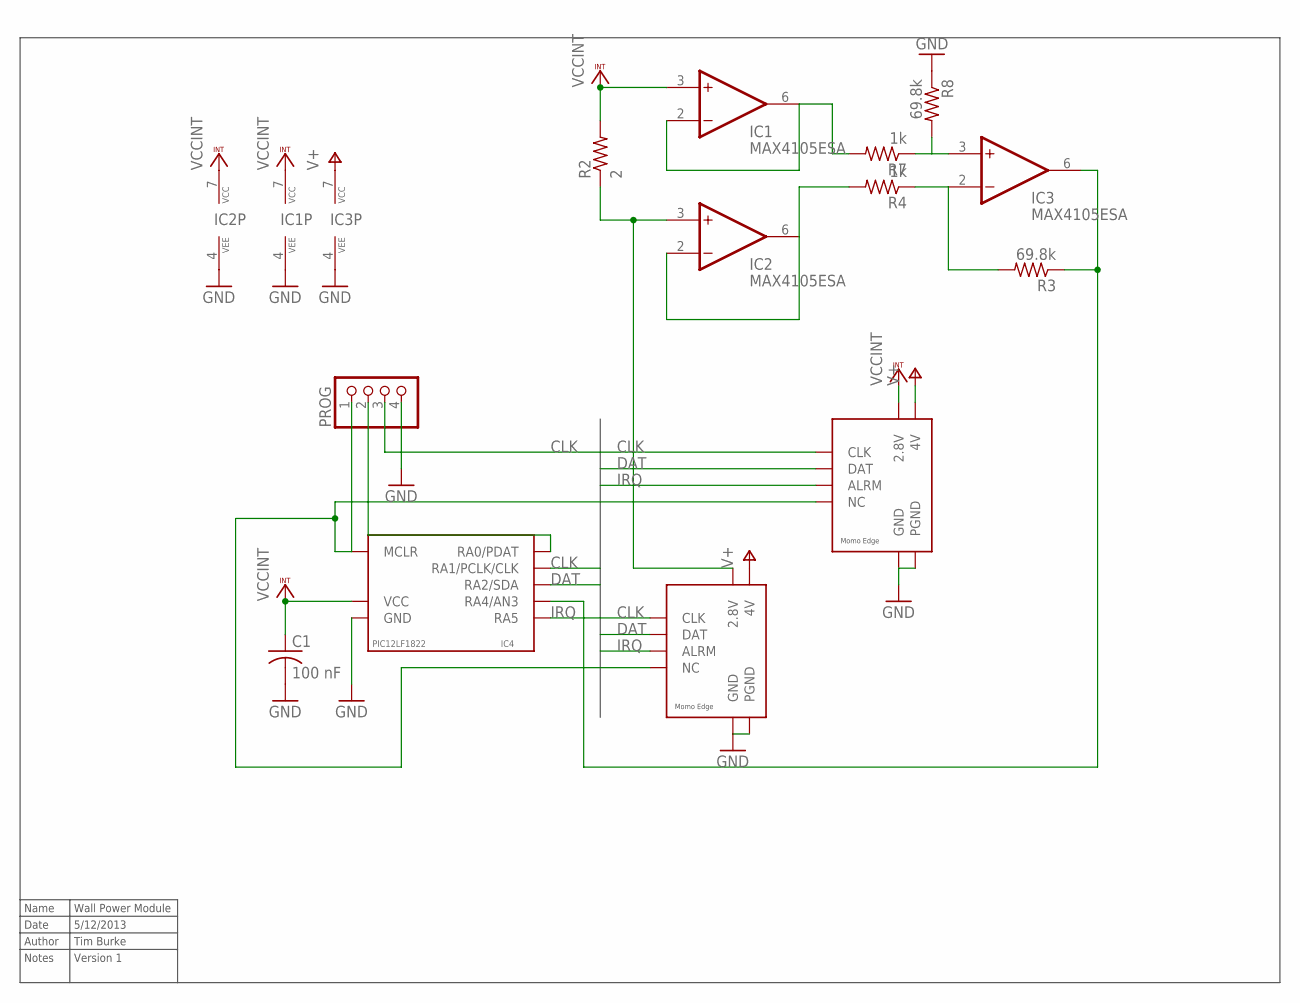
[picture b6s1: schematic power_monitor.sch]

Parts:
C1: 100 nF; C0402
IC1, IC2, IC3: MAX4105ESA; SO08
IC4: PIC12LF1822; SOIC8
PROG: PINHD-1X4; 1X04
R2: 2; R0603
R3, R8: 69.8k; R0603
R4, R7: 1k; R0603
U$6: MOMO-EDGE-8F
U$7: MOMO-EDGE-8M

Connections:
CLK: IC4.6 (RA1/PCLK/CLK), PROG.3, U$6.CLK, U$7.CLK
DAT: IC4.5 (RA2/SDA), U$6.DAT, U$7.DAT
GND: C1.2, IC1.4 (VEE), IC2.4 (VEE), IC3.4 (VEE), IC4.8 (GND), PROG.4, R8.1, U$6.GND, U$6.PGND, U$7.GND, U$7.PGND
IRQ: IC4.2 (RA5), U$6.ARLM (ALRM), U$7.ALRM
unnamed: IC4.4 (MCLR), PROG.1, U$6.NV (NC), U$7.NC
unnamed: IC3.6 (OUT), IC4.3 (RA4/AN3), R3.1
unnamed: IC2.2 (-IN), IC2.6 (OUT), R4.2
unnamed: IC1.2 (-IN), IC1.6 (OUT), R7.2
unnamed: IC3.2 (-IN), R3.2, R4.1
unnamed: IC4.7 (RA0/PDAT), PROG.2
unnamed: IC3.3 (+IN), R7.1, R8.2
unnamed: IC2.3 (+IN), R2.1, U$7.V28 (2.8V)
V+: IC3.7 (VCC), U$6.V4. (4V), U$7.V4 (4V)
VCCINT: C1.1, IC1.3 (+IN), IC1.7 (VCC), IC2.7 (VCC), IC4.1 (VCC), R2.2, U$6.V28 (2.8V)

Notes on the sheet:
Name
Wall Power Module
Date
5/12/2013
Author
Tim Burke
Notes
Version 1
